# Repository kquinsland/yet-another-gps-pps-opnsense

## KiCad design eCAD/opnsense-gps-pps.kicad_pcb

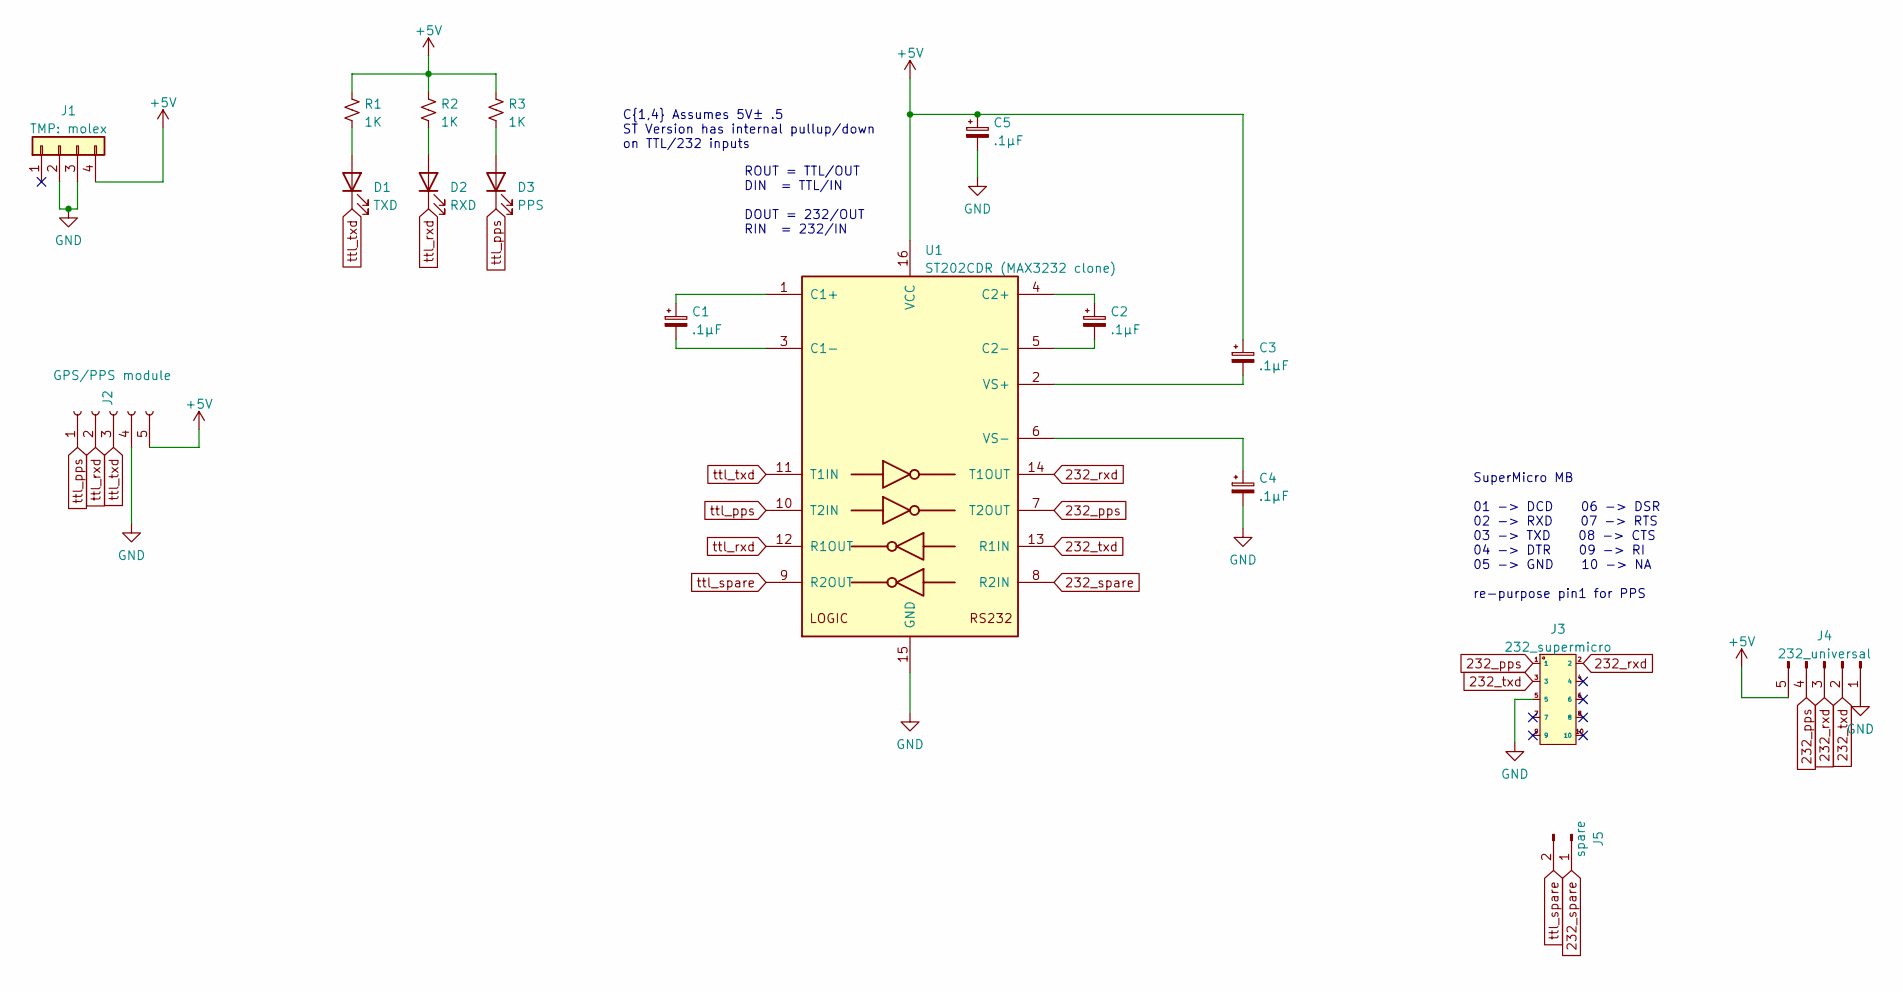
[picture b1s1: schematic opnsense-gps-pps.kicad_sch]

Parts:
C1, C2, C3, C4, C5: .1μF; C_0805_2012Metric_Pad1.18x1.45mm_HandSolder; LCSC_PN C28233
D1: TXD; LED_0805_2012Metric_Pad1.15x1.40mm_HandSolder; LCSC_PN C84256
D2: RXD; LED_0805_2012Metric_Pad1.15x1.40mm_HandSolder; LCSC_PN C84256
D3: PPS; LED_0805_2012Metric_Pad1.15x1.40mm_HandSolder; LCSC_PN C84256
J1: TMP: molex; AMP 1-480426-0 (4 pin atx molex)
J2: GPS/PPS module; PinSocket_1x05_P2.54mm_Horizontal; LCSC_PN C2935995
J3: 232_supermicro; 878311020; LCSC_PN C588620
J4: 232_universal; PinHeader_1x05_P2.54mm_Vertical
J5: spare; PinHeader_1x02_P2.54mm_Vertical
R1, R2, R3: 1K; R_0805_2012Metric_Pad1.20x1.40mm_HandSolder; LCSC_PN C17513
U1: ST202CDR (MAX3232 clone); SOIC-16_3.9x9.9mm_P1.27mm; LCSC_PN C6867

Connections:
232_pps: J3.1, J4.4, U1.7 (T2OUT)
232_rxd: J3.2, J4.3, U1.14 (T1OUT)
232_spare: J5.1, U1.8 (R2IN)
232_txd: J3.3, J4.2, U1.13 (R1IN)
+5V: C3.1, C5.1, J1.4, J2.5, J4.5, R1.1, R2.1, R3.1, U1.16 (VCC)
GND: C4.2, C5.2, J1.2, J1.3, J2.4, J3.5, J4.1, U1.15 (GND)
unnamed: C1.1, U1.1 (C1+)
unnamed: C1.2, U1.3 (C1-)
unnamed: C2.1, U1.4 (C2+)
unnamed: C2.2, U1.5 (C2-)
unnamed: C3.2, U1.2 (VS+)
unnamed: C4.1, U1.6 (VS-)
unnamed: D1.2 (A), R1.2
unnamed: D2.2 (A), R2.2
unnamed: D3.2 (A), R3.2
ttl_pps: D3.1 (K), J2.1, U1.10 (T2IN)
ttl_rxd: D2.1 (K), J2.2, U1.12 (R1OUT)
ttl_spare: J5.2, U1.9 (R2OUT)
ttl_txd: D1.1 (K), J2.3, U1.11 (T1IN)

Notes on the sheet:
C{1,4} Assumes 5V± .5 ST Version has internal pullup/down on TTL/232 inputs
ROUT = TTL/OUT DIN = TTL/IN DOUT = 232/OUT RIN = 232/IN
SuperMicro MB 01 -> DCD 06 -> DSR 02 -> RXD 07 -> RTS 03 -> TXD 08 -> CTS 04 -> DTR 09 -> RI 05 -> GND 10 -> NA re-purpose pin1 for PPS

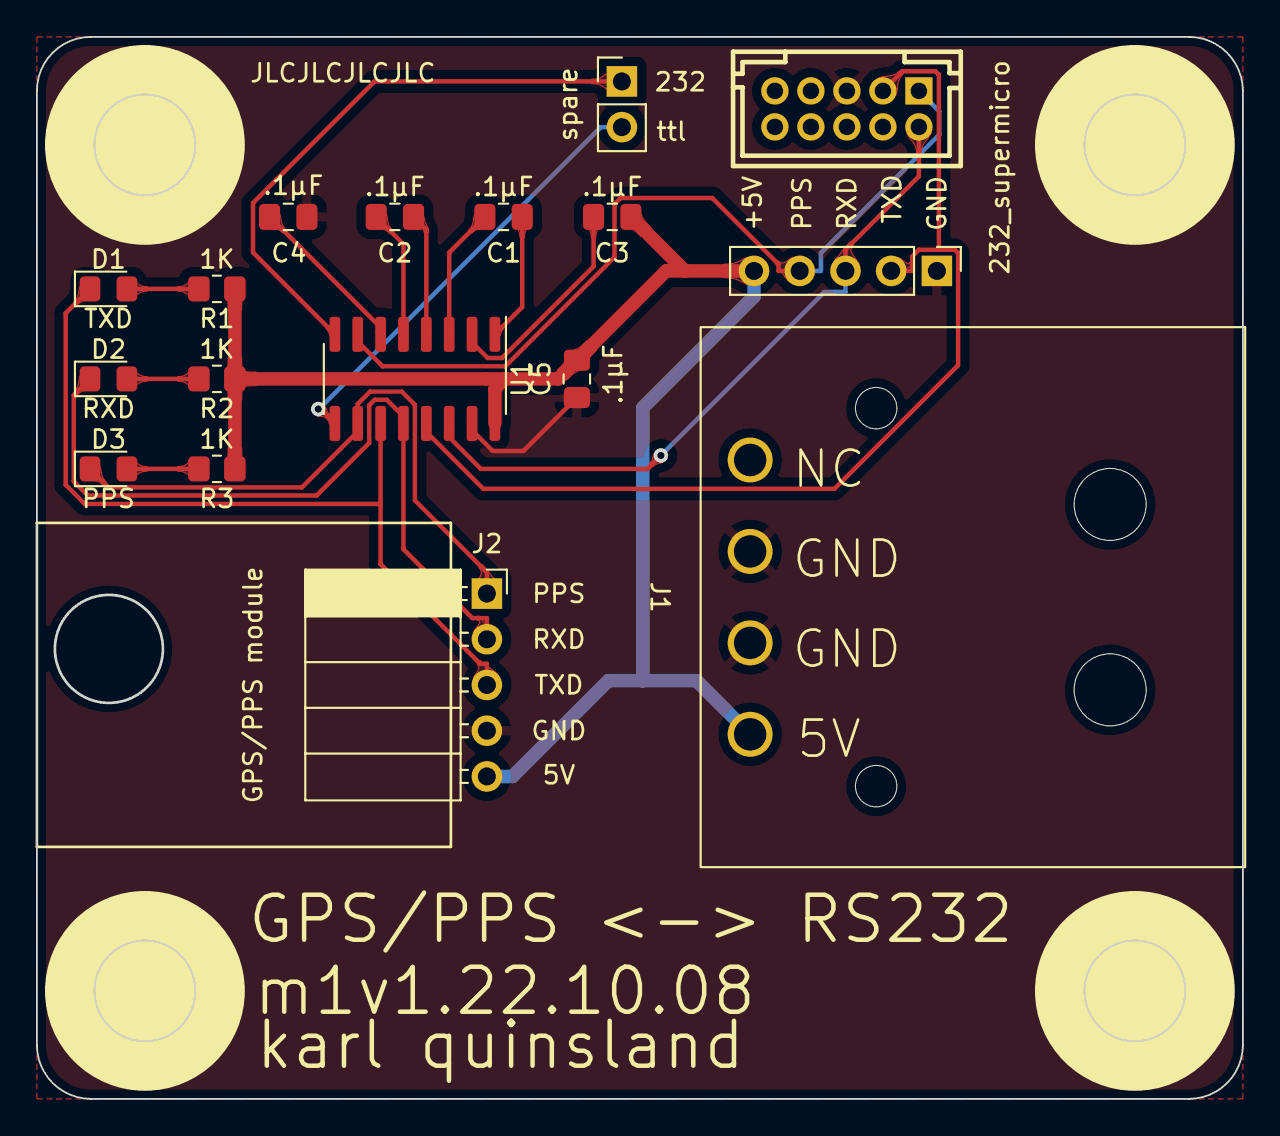
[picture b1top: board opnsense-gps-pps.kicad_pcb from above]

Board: 2 copper layers, 67.0 x 58.9 mm, 17 parts (0 on the bottom side), 19 nets.

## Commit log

2022-10-15 Initial read me draft
2022-10-15 Add KiCad files / exports
2022-10-15 Add uBlox data sheet and schematic PDF
2022-10-15 add mechanical CAD files
2022-10-15 Add main readme
    And processed pictures
